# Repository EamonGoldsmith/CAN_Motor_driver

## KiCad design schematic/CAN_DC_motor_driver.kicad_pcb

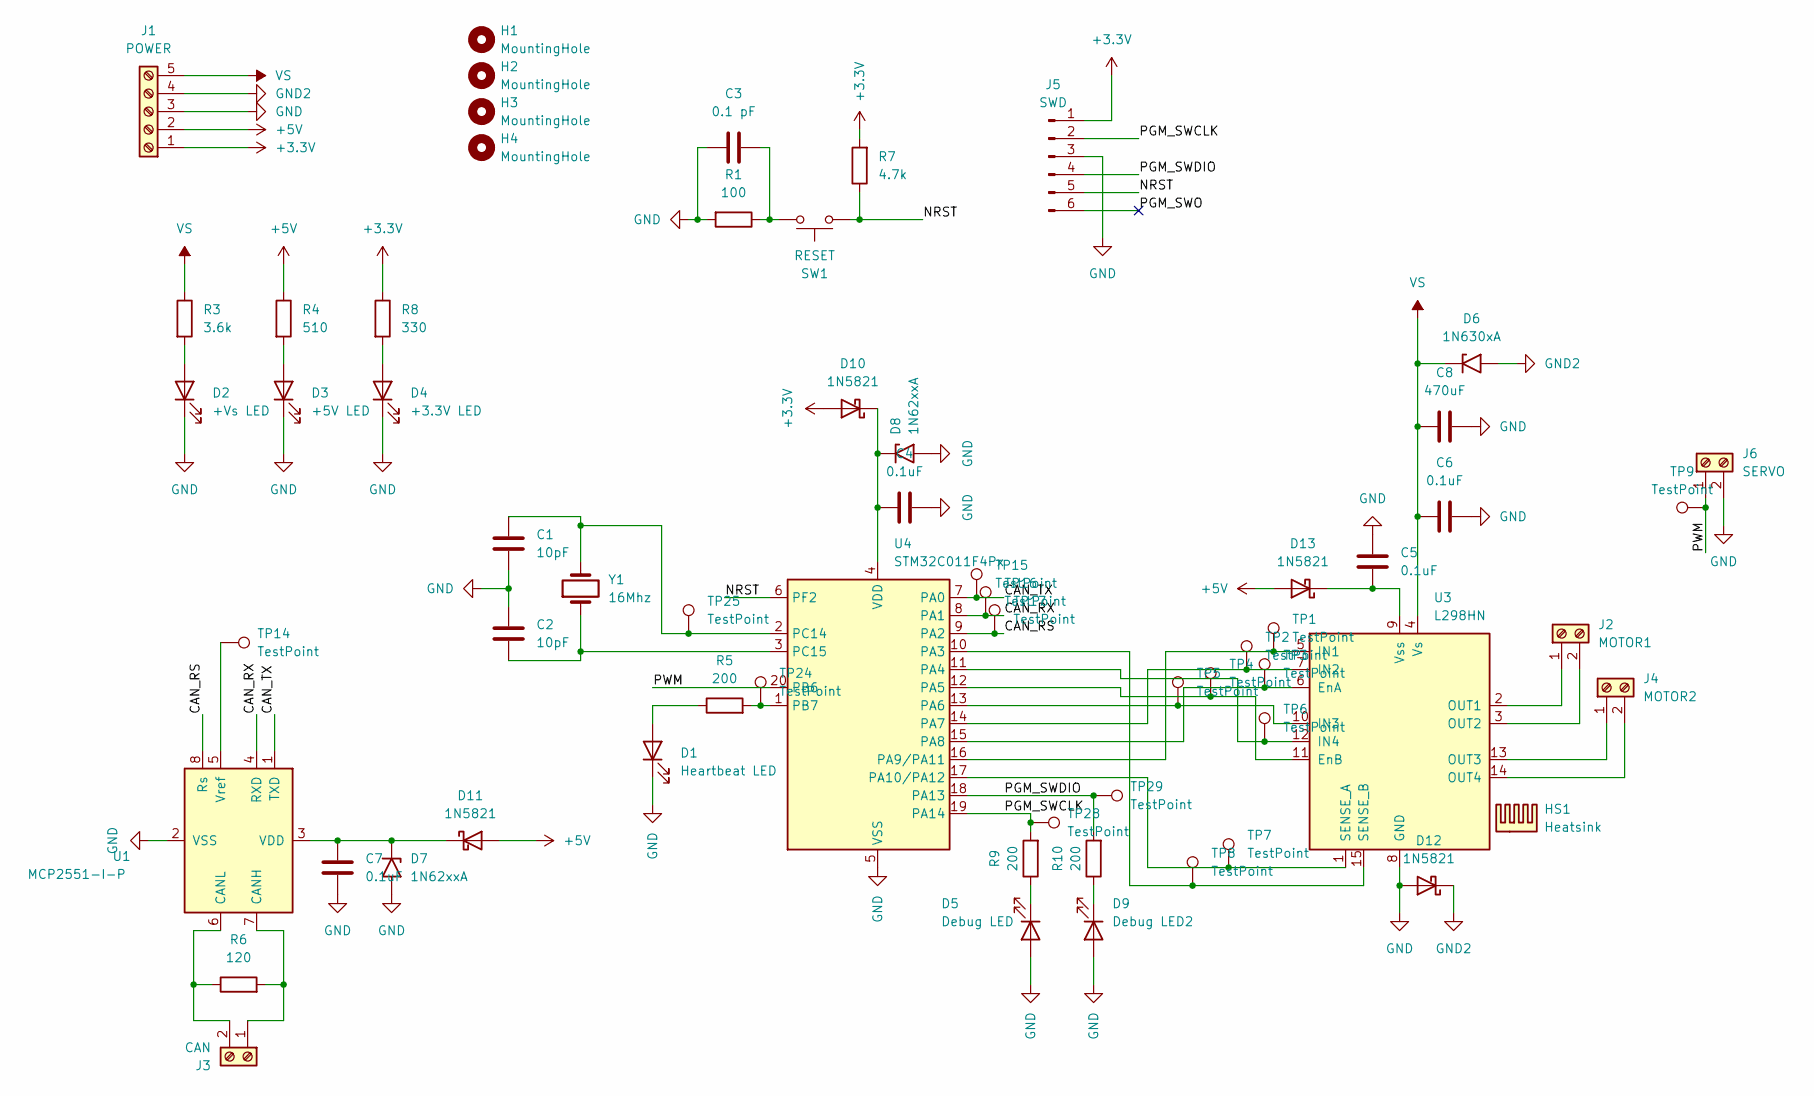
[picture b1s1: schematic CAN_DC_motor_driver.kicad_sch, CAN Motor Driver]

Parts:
C1: 10pF; MountingHole_4.3mm_M4
C2: 10pF; C_Axial_L3.8mm_D2.6mm_P7.50mm_Horizontal
C3: 0.1 pF; C_Axial_L3.8mm_D2.6mm_P7.50mm_Horizontal
C4, C5, C6, C7: 0.1uF; C_Axial_L3.8mm_D2.6mm_P7.50mm_Horizontal
C8: 470uF; C_Axial_L3.8mm_D2.6mm_P7.50mm_Horizontal
D1: Heartbeat LED; LED_D5.0mm
D2: +Vs LED; LED_D5.0mm
D3: +5V LED; LED_D5.0mm
D4: +3.3V LED; LED_D5.0mm
D5: Debug LED; LED_D5.0mm
D6: 1N630xA; D_DO-201AE_P15.24mm_Horizontal
D7, D8: 1N62xxA; D_DO-201AE_P15.24mm_Horizontal
D9: Debug LED2; LED_D5.0mm
D10, D11, D12, D13: 1N5821; D_DO-201AD_P15.24mm_Horizontal
H1, H2, H3, H4: MountingHole; MountingHole_4.3mm_M4
HS1: Heatsink; Heatsink_Fischer_FK224xx2201_25x8.3mm
J1: POWER; TerminalBlock_bornier-5_P5.08mm
J2: MOTOR1; TerminalBlock_bornier-2_P5.08mm
J3: CAN; TerminalBlock_bornier-2_P5.08mm
J4: MOTOR2; TerminalBlock_bornier-2_P5.08mm
J5: SWD; PinSocket_1x06_P2.54mm_Vertical
J6: SERVO; TerminalBlock_bornier-2_P5.08mm
R1: 100; R_Axial_DIN0204_L3.6mm_D1.6mm_P7.62mm_Horizontal
R3: 3.6k; R_Axial_DIN0204_L3.6mm_D1.6mm_P7.62mm_Horizontal
R4: 510; R_Axial_DIN0204_L3.6mm_D1.6mm_P7.62mm_Horizontal
R5, R9, R10: 200; R_Axial_DIN0204_L3.6mm_D1.6mm_P7.62mm_Horizontal
R6: 120; R_Axial_DIN0204_L3.6mm_D1.6mm_P7.62mm_Horizontal
R7: 4.7k; R_Axial_DIN0204_L3.6mm_D1.6mm_P7.62mm_Horizontal
R8: 330; R_Axial_DIN0204_L3.6mm_D1.6mm_P7.62mm_Horizontal
SW1: RESET; SW_PUSH_6mm
TP1, TP2, TP3, TP4, TP5, TP6, TP7, TP8, TP9, TP14, TP15, TP16, TP17, TP24, TP25, TP28, TP29: TestPoint; TestPoint_Pad_D1.0mm
U1: MCP2551-I-P; DIP-8_W7.62mm
U3: L298HN; TO-220-15_P2.54x2.54mm_StaggerOdd_Lead5.84mm_TabDown
U4: STM32C011F4Px; TSSOP-20_4.4x6.5mm_P0.65mm
Y1: 16Mhz; Crystal_HC18-U_Vertical

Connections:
+3.3V: D10.2 (A), J1.1, J5.1, R7.2, R8.1
+5V: D11.2 (A), D13.2 (A), J1.2, R4.1
/CAN_RS: TP17.1, U1.8 (Rs), U4.9 (PA2)
/CAN_RX: TP16.1, U1.4 (RXD), U4.8 (PA1)
/CAN_TX: TP15.1, U1.1 (TXD), U4.7 (PA0)
/NRST: J5.5, R7.1, SW1.1, U4.6 (PF2)
/PGM_SWCLK: J5.2, R9.2, TP28.1, U4.19 (PA14)
/PGM_SWDIO: J5.4, R10.2, TP29.1, U4.18 (PA13)
/PGM_SWO: J5.6
/PWM: J6.1, TP9.1, U4.20 (PB6)
GND: C1.2, C2.1, C3.1, C4.2, C5.1, C6.2, C7.2, C8.2, D1.1 (K), D2.1 (K), D3.1 (K), D4.1 (K), D5.2 (A), D7.2 (A2), D8.2 (A2), D9.2 (A), D12.2 (A), J1.3, J5.3, J6.2, R1.2, U1.2 (VSS), U3.8 (GND), U4.5 (VSS)
GND2: D6.2 (A2), D12.1 (K), J1.4
unnamed: C3.2, R1.1, SW1.2
unnamed: D1.2 (A), R5.1
unnamed: D2.2 (A), R3.2
unnamed: D3.2 (A), R4.2
unnamed: D4.2 (A), R8.2
unnamed: D5.1 (K), R9.1
unnamed: D9.1 (K), R10.1
unnamed: C4.1, D8.1 (A1), D10.1 (K), U4.4 (VDD)
unnamed: C7.1, D7.1 (A1), D11.1 (K), U1.3 (VDD)
unnamed: C5.2, D13.1 (K), U3.9 (Vss)
unnamed: J2.1, U3.2 (OUT1)
unnamed: J2.2, U3.3 (OUT2)
unnamed: J3.1, R6.2, U1.7 (CANH)
unnamed: J3.2, R6.1, U1.6 (CANL)
unnamed: J4.1, U3.13 (OUT3)
unnamed: J4.2, U3.14 (OUT4)
unnamed: TP14.1, U1.5 (Vref)
unnamed: TP3.1, U3.6 (EnA), U4.15 (PA8)
unnamed: TP4.1, U3.11 (EnB), U4.12 (PA5)
unnamed: TP1.1, U3.5 (IN1), U4.16 (PA9/PA11)
unnamed: TP2.1, U3.7 (IN2), U4.14 (PA7)
unnamed: TP5.1, U3.10 (IN3), U4.13 (PA6)
unnamed: TP6.1, U3.12 (IN4), U4.11 (PA4)
unnamed: TP7.1, U3.1 (SENSE_A), U4.17 (PA10/PA12)
unnamed: TP8.1, U3.15 (SENSE_B), U4.10 (PA3)
unnamed: R5.2, TP24.1, U4.1 (PB7)
unnamed: C1.1, TP25.1, U4.2 (PC14), Y1.2
unnamed: C2.2, U4.3 (PC15), Y1.1
VS: C6.1, C8.1, D6.1 (A1), J1.5, R3.1, U3.4 (Vs)

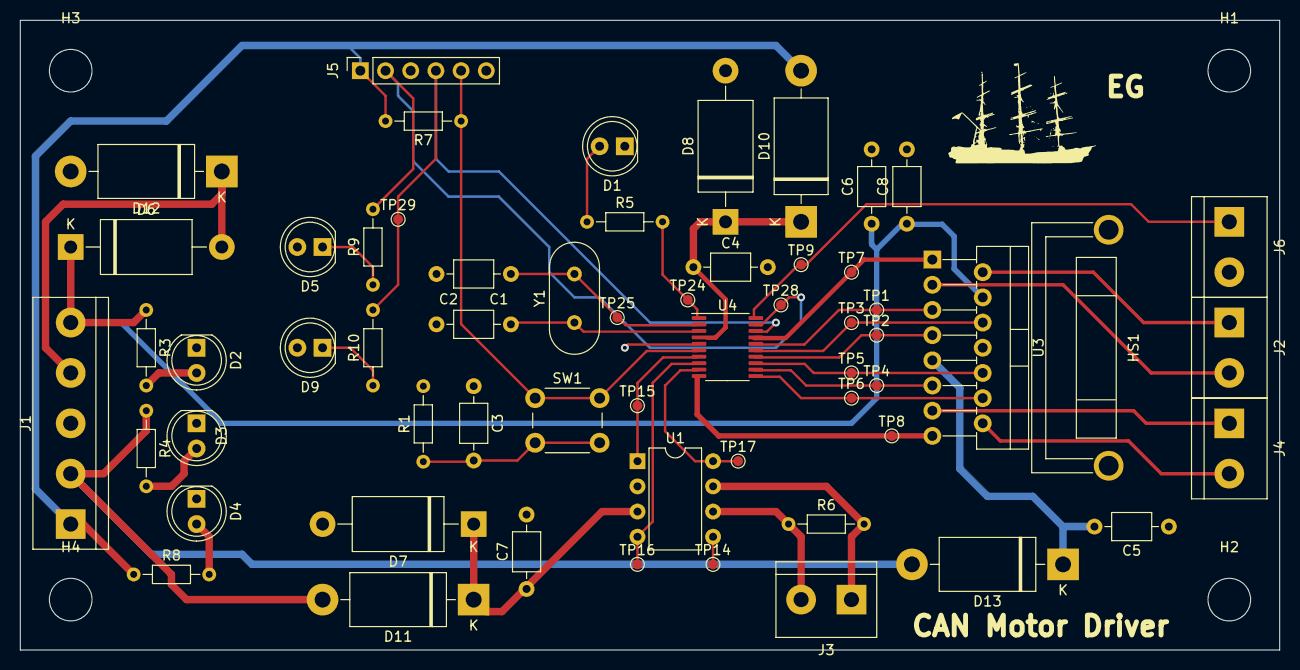
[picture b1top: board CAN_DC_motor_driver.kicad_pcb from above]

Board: 2 copper layers, 127.0 x 63.5 mm, 63 parts (0 on the bottom side), 40 nets.

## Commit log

2024-03-01 init - files via upload
2024-03-01 init
    pcb layout and schematic files
2024-03-01 images
    for readme
2024-03-01 fixed images
2024-03-01 fixed image cropping
